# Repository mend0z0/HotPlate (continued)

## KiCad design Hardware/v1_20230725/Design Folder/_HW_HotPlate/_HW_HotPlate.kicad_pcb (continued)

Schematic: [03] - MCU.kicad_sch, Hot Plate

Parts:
C301, C302: 12pF_50V_C0G; C_0201_0603Metric; Part Number (Manufactur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 CC0201JRNPO9BN120
C303, C304, C306, C308, C309, C311: 100nF_6V3_X7R; C_0201_0603Metric; Part Number (Manufactur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 CC0201KRX7R5BB104
C305, C307, C310: 10uF_16V_X5R; C_0603_1608Metric; Part Number (Manufactur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 GRT188R61C106KE13J
D301: SMF3.3_3.3V_30A; D_SOD-123F; Part Number (Manufactur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 SMF3.3
J301: MHDR_4X1_RA_2.54MM; PinSocket_1x04_P2.54mm_Horizontal; Part Number (Manufactur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 PH1RB-04-UA
LED301: RED_2V_0.02A; LED_0402_1005Metric; Part Number (Manufactur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 B2841USD-20D001014U1930
R301: 49R9_1/20W_1%; R_0201_0603Metric; Part Number (Manufactur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 RMCF0201FT49R9
R302: 10KR_1/20W_1%; R_0201_0603Metric; Part Number (Manufactur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 RMCF0201FT10K0
R303: 100R_1/20W_1%; R_0201_0603Metric; Part Number (Manufactur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 RMCF0201FT100R
U301: PIC18F24J50-I/ML; QFN-28-1EP_6x6mm_P0.65mm_EP4.25x4.25mm_ThermalVias; Part Number (Manufactur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 PIC18F24J50-I/ML
U302, U303: SN74LVC1G17DBVR; SOT-23-5; Part Number (Manufactur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 SN74LVC1G17DBVR
X301: 16MHz_10ppm_12pF; Crystal_SMD_2016-4Pin_2.0x1.6mm; Part Number (Manufactur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 ECS-160-12-37B-CTN-TR

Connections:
/BLOCK DIAGRAM/FAN DRIVER/EN_FAN: U301.9 (RC1/T1OSI/UOE/RP12); also elsewhere on the board
/BLOCK DIAGRAM/ISOLATED TRIAC DRIVER/+3V3_1: C303.1, C307.1, C308.1, C309.1, C310.1, C311.1, R302.1, U301.11 (VUSB), U301.17 (VDD), U302.5 (VCC), U303.5 (VCC); also elsewhere on the board
/BLOCK DIAGRAM/ISOLATED TRIAC DRIVER/EN_TRIAC: U301.8 (RC0/T1OSO/T1CKI/RP11); also elsewhere on the board
/BLOCK DIAGRAM/ISOLATED TRIAC DRIVER/MAIN_STROBE: U301.21 (RB3/AN9/CTED2/VPO/RP6); also elsewhere on the board
/BLOCK DIAGRAM/LEDS DRIVER/SIG_LED_AMBER: U301.1 (RA2/AN2/VREF-/CVREF/C2INB); also elsewhere on the board
/BLOCK DIAGRAM/LEDS DRIVER/SIG_LED_BLUE: U301.28 (RA1/AN1/C2INA/RP1); also elsewhere on the board
/BLOCK DIAGRAM/LEDS DRIVER/SIG_LED_RED: U301.27 (RA0/AN0/C1INA/ULPWU/RP0); also elsewhere on the board
/BLOCK DIAGRAM/MICROCONTROLLER/ENCODER_PB: U301.18 (RB0/AN12/INT0/RP3); also elsewhere on the board
/BLOCK DIAGRAM/MICROCONTROLLER/EN_PWR: U301.10 (RC2/AN11/CTPLS/RP13); also elsewhere on the board
/BLOCK DIAGRAM/MICROCONTROLLER/MAX31855_SO: U301.23 (RB5/KBI1/SDI1/SDA1/RP8); also elsewhere on the board
/BLOCK DIAGRAM/MICROCONTROLLER/MAX31855_~CS: U301.14 (RC6/TX1/CK1/RP17); also elsewhere on the board
/BLOCK DIAGRAM/MICROCONTROLLER/PCD8544_D/C: U301.20 (RB2/AN8/CTED1/VMO/REFO/RP5); also elsewhere on the board
/BLOCK DIAGRAM/MICROCONTROLLER/PCD8544_~CE: U301.4 (RA5/AN4/SS1/HLVDIN/RCV/RP2); also elsewhere on the board
/BLOCK DIAGRAM/MICROCONTROLLER/PIC18_ICSPPGC: J301.3, U301.24 (RB6/KBI2/PGC/RP9); also elsewhere on the board
/BLOCK DIAGRAM/MICROCONTROLLER/PIC_OSC1: C301.1, U301.6 (OSC1/CLKI/RA7), X301.1
/BLOCK DIAGRAM/MICROCONTROLLER/PIC_OSC2: R301.2, U301.7 (OSC2/CLKO/RA6)
/BLOCK DIAGRAM/MICROCONTROLLER/PIC_SCK1: U301.22 (RB4/KBI0/SCK1/SCL1/RP7), U302.2 (A)
/BLOCK DIAGRAM/MICROCONTROLLER/PIC_SDO1: U301.15 (RC7/RX1/DT1/SDO1/RP18), U303.2 (A)
/BLOCK DIAGRAM/MICROCONTROLLER/PIC_VDDCORE: C305.1, C306.1, U301.3 (VDDCORE/VCAP(2))
/BLOCK DIAGRAM/MICROCONTROLLER/PIC_~MCLR: C304.1, D301.1, J301.1, R302.2, U301.26 (~MCLR)
/BLOCK DIAGRAM/MICROCONTROLLER/SPI_SCK: U302.4 (Y); also elsewhere on the board
/BLOCK DIAGRAM/MICROCONTROLLER/USB_DM: U301.12 (RC4/D-/VM); also elsewhere on the board
/BLOCK DIAGRAM/MICROCONTROLLER/USB_DP: U301.13 (RC5/D+/VP); also elsewhere on the board
/BLOCK DIAGRAM/PCD8544 Driver/MOSI: U303.4 (Y); also elsewhere on the board
/BLOCK DIAGRAM/PCD8544 Driver/RST: U301.19 (RB1/AN10/RTCC/RP4); also elsewhere on the board
unnamed: C302.1, R301.1, X301.3
unnamed: LED301.2, R303.2
unnamed: R303.1, U301.2 (RA3/AN3/VREF+/C1INB)

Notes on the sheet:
I = 250mA @ +3V3DC
DESIGN NOTE:
1: The on-chip voltage regulator is only available on parts designated with an “F”, such as PIC18F25J50. The on-chip regulator is disabled on devices with “LF” in their part number. 2: The VDDCORE/VCAP pin must never be left floating. On “F” devices, it must be connected to a capacitor, of size, CE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
ISCP PROGRAMMER PINS

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
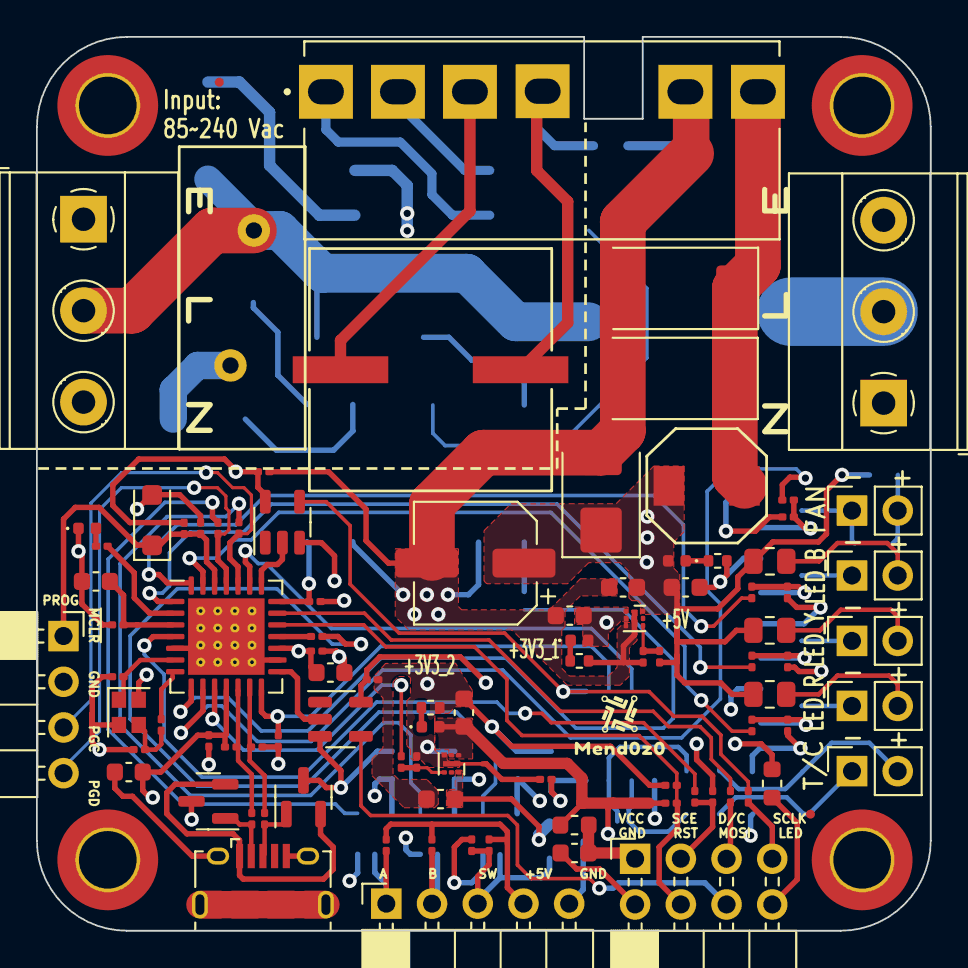
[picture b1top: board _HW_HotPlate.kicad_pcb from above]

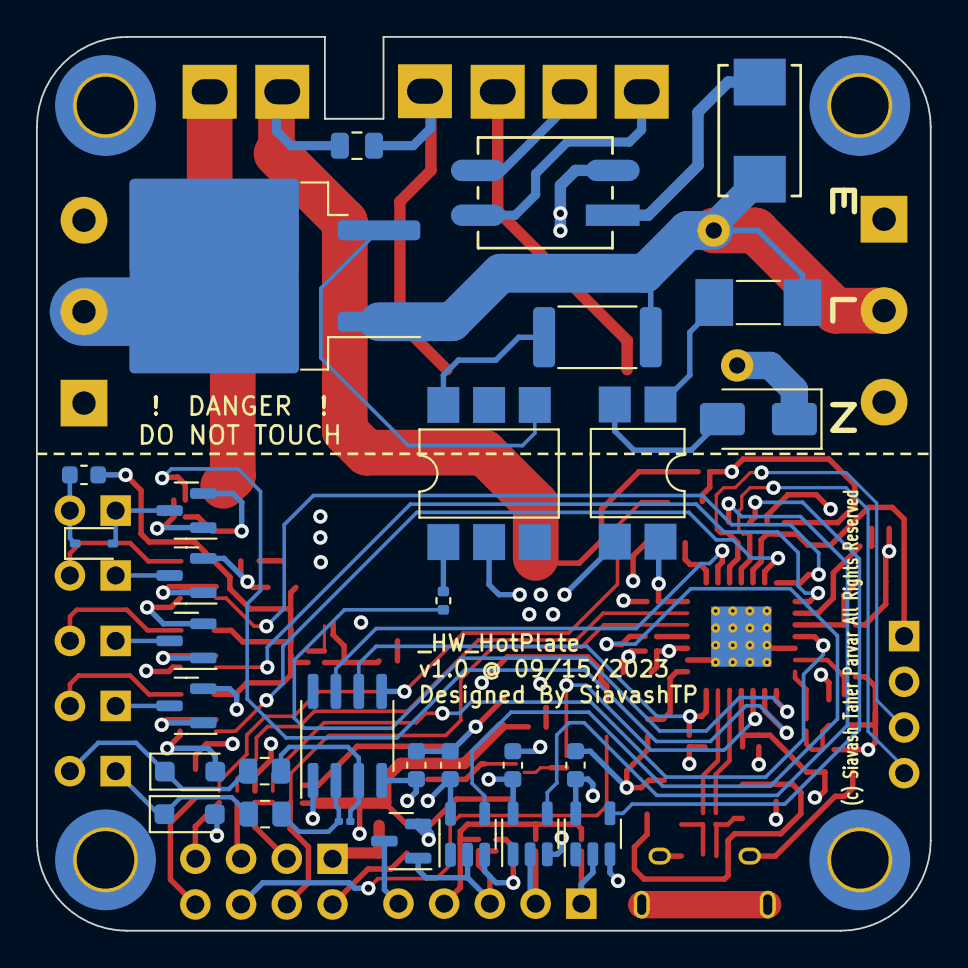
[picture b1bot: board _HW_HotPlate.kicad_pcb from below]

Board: 4 copper layers, 49.7 x 49.7 mm, 129 parts (30 on the bottom side), 82 nets.

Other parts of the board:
J801: RECEPT_2X1_VERT_2.54MM; PinSocket_1x02_P2.54mm_Vertical
R904, R905, R906: 100R_1/20W_1%; R_0201_0603Metric
R907, R908, R909: 10KR_1/20W_1%; R_0201_0603Metric

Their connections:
/BLOCK DIAGRAM/LEDS DRIVER/SIG_LED_AMBER: R905.1; also elsewhere on the board
/BLOCK DIAGRAM/LEDS DRIVER/SIG_LED_BLUE: R906.1; also elsewhere on the board
/BLOCK DIAGRAM/LEDS DRIVER/SIG_LED_RED: R904.1; also elsewhere on the board

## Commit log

2023-09-30 File restructuring
2023-10-01 Some cleanup
2023-11-20 Sorting documents
2023-12-24 Adding Block Diagrams
2023-12-25 Firmware has been added
2023-12-25 Adding screenshots
2023-12-25 Some modification for screenshots
2023-12-25 Adding hardware block diagram
2023-12-25 Adding Firmware block digram
2023-12-25 Updating block diagrams
2023-12-27 Updating BlockDiagrams
2023-12-27 Updating naming
2023-12-27 Updating files naming
2023-12-27 Updating file naming
2023-12-29 Schematic library has been updated
2023-12-29 components have been updated
2023-12-29 Updating hardware format structure
2023-12-29 Updating the symbols' structure
2023-12-29 Adding some folders
2024-01-04 Updating file structures
2024-01-05 Updating README.md
2024-01-07 Library updated
2024-01-09 Adding Firmware block diagram
2024-01-13 Some try to check the working condition of assembled MCU
2024-01-15 Adding assembled pictures
2024-01-16 Updating assembled pictures
2024-01-16 Adding main files to the firmware project
2024-01-16 Adding the list of work needs to be done
2024-01-17 Adding some items to todo list
2024-01-17 A little bit of change in naming convention for pictures
2024-01-19 A little change in folder structures
2024-01-21 Designing the Mechanical parts
2024-01-23 Working on the 3D CAD model
2024-02-03 Working on 3D CAD model
2024-02-04 3D CAD Model has been created
2024-02-04 Some measurements have been added in PCB
2024-02-04 Some more update to 3D CAD model
